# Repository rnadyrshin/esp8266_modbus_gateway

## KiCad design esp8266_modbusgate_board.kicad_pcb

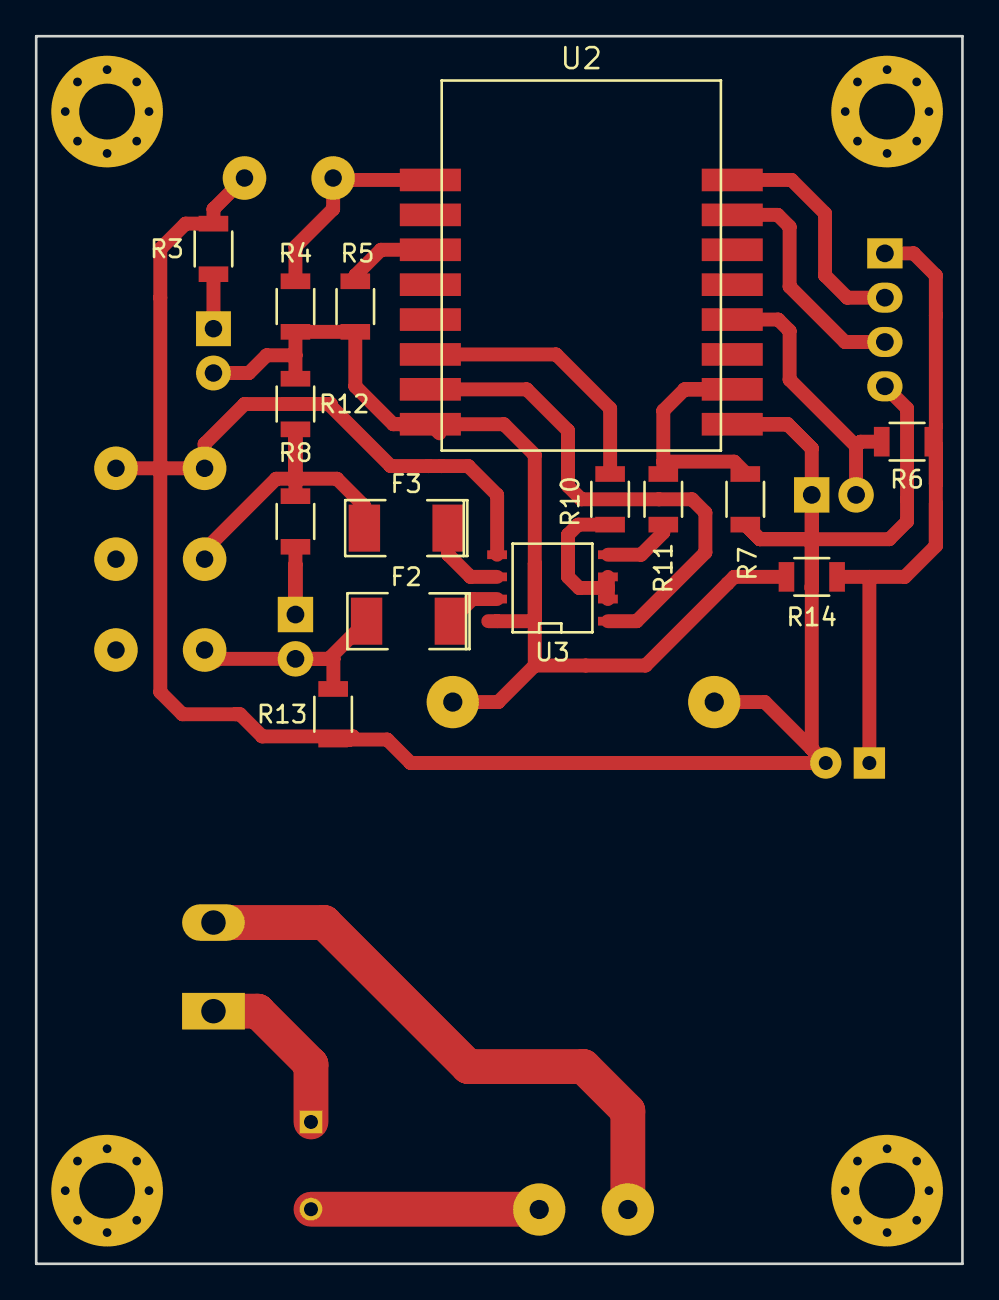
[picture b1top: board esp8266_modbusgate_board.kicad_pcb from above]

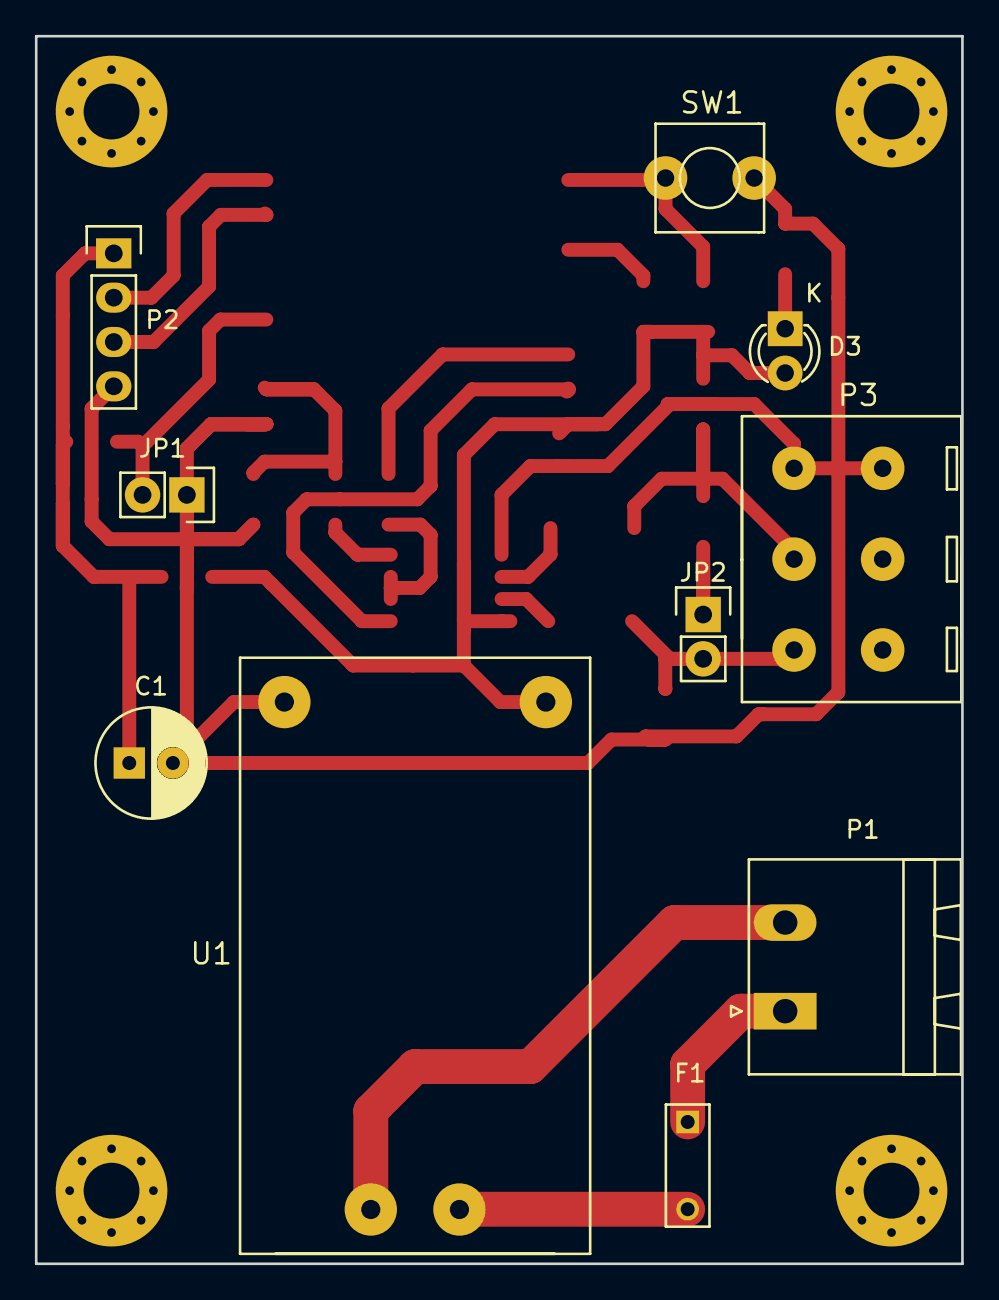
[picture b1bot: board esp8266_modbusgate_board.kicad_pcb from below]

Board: 2 copper layers, 53.1 x 70.4 mm, 25 parts (10 on the bottom side), 17 nets.

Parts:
C1: CP; C_Radial_D6.3_L11.2_P2.5
D3: Led_Small; LED-3MM
F1: F_Small; C_Rect_L7_W2.5_P5
F2, F3: F_Small; SMD-2010_Pol
JP1, JP2: Jumper_NO_Small; Pin_Header_Straight_1x02
P1: CONN_01X02; PhoenixContact_MSTBA-G_02x5.08mm_Angled
P2: CONN_01X04; Pin_Header_Straight_1x04
P3: CONN_01X03; CONN
R3, R4, R5, R6, R7: 1K; R_1206
R8: 120; R_1206
R10, R11, R14: 0; R_1206
R12, R13: 10K; R_1206
SW1: SW_PUSH_SMALL_H; BTN
U1: HLK-PMxx
U2: ESP-07
U3: AD3485; SOIC-8-N

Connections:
+3V3: C1.1, D3.2 (A), P2.1, R4.2, R5.2, R6.2, R12.2, R14.1, R14.2, U1.3 (+Vo), U2.8 (VCC), U3.8
GND: C1.2, JP1.1, P2.4, P3.3, R3.2, R7.2, R13.1, SW1.2, U1.4 (-Vo), U2.9 (GND), U3.5
unnamed: D3.1 (K), R3.1
unnamed: F1.2, U1.2 (AC)
unnamed: JP2.1, R8.2
unnamed: F1.1, P1.1
unnamed: P1.2, U1.1 (AC)
unnamed: P2.2, U2.16 (TXD0)
unnamed: P2.3, U2.15 (RXD0)
unnamed: F2.2, JP2.2, P3.1, R13.2
unnamed: F3.2, P3.2, R8.1, R12.1
unnamed: U3.2, U3.3
unnamed: R5.1, U2.3 (EN)
unnamed: JP1.2, R6.1, U2.12 (GPIO00)
unnamed: R10.1, U2.6 (GPIO12)
unnamed: R7.1, R11.1, U2.10 (GPIO15)
unnamed: R4.1, SW1.1, U2.1 (RST)
